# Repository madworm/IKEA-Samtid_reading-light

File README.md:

IKEA-Samtid_reading-light (WIP)
===============================

LAYOUT FILES: Circuit board to go between the movable beams of the Samtid lamp.

---

Before having PC-boards made, please make sure you know about your manufacturer's peculiarities!
Especially drill-sizes and their tolerances may vary too much and give you trouble.

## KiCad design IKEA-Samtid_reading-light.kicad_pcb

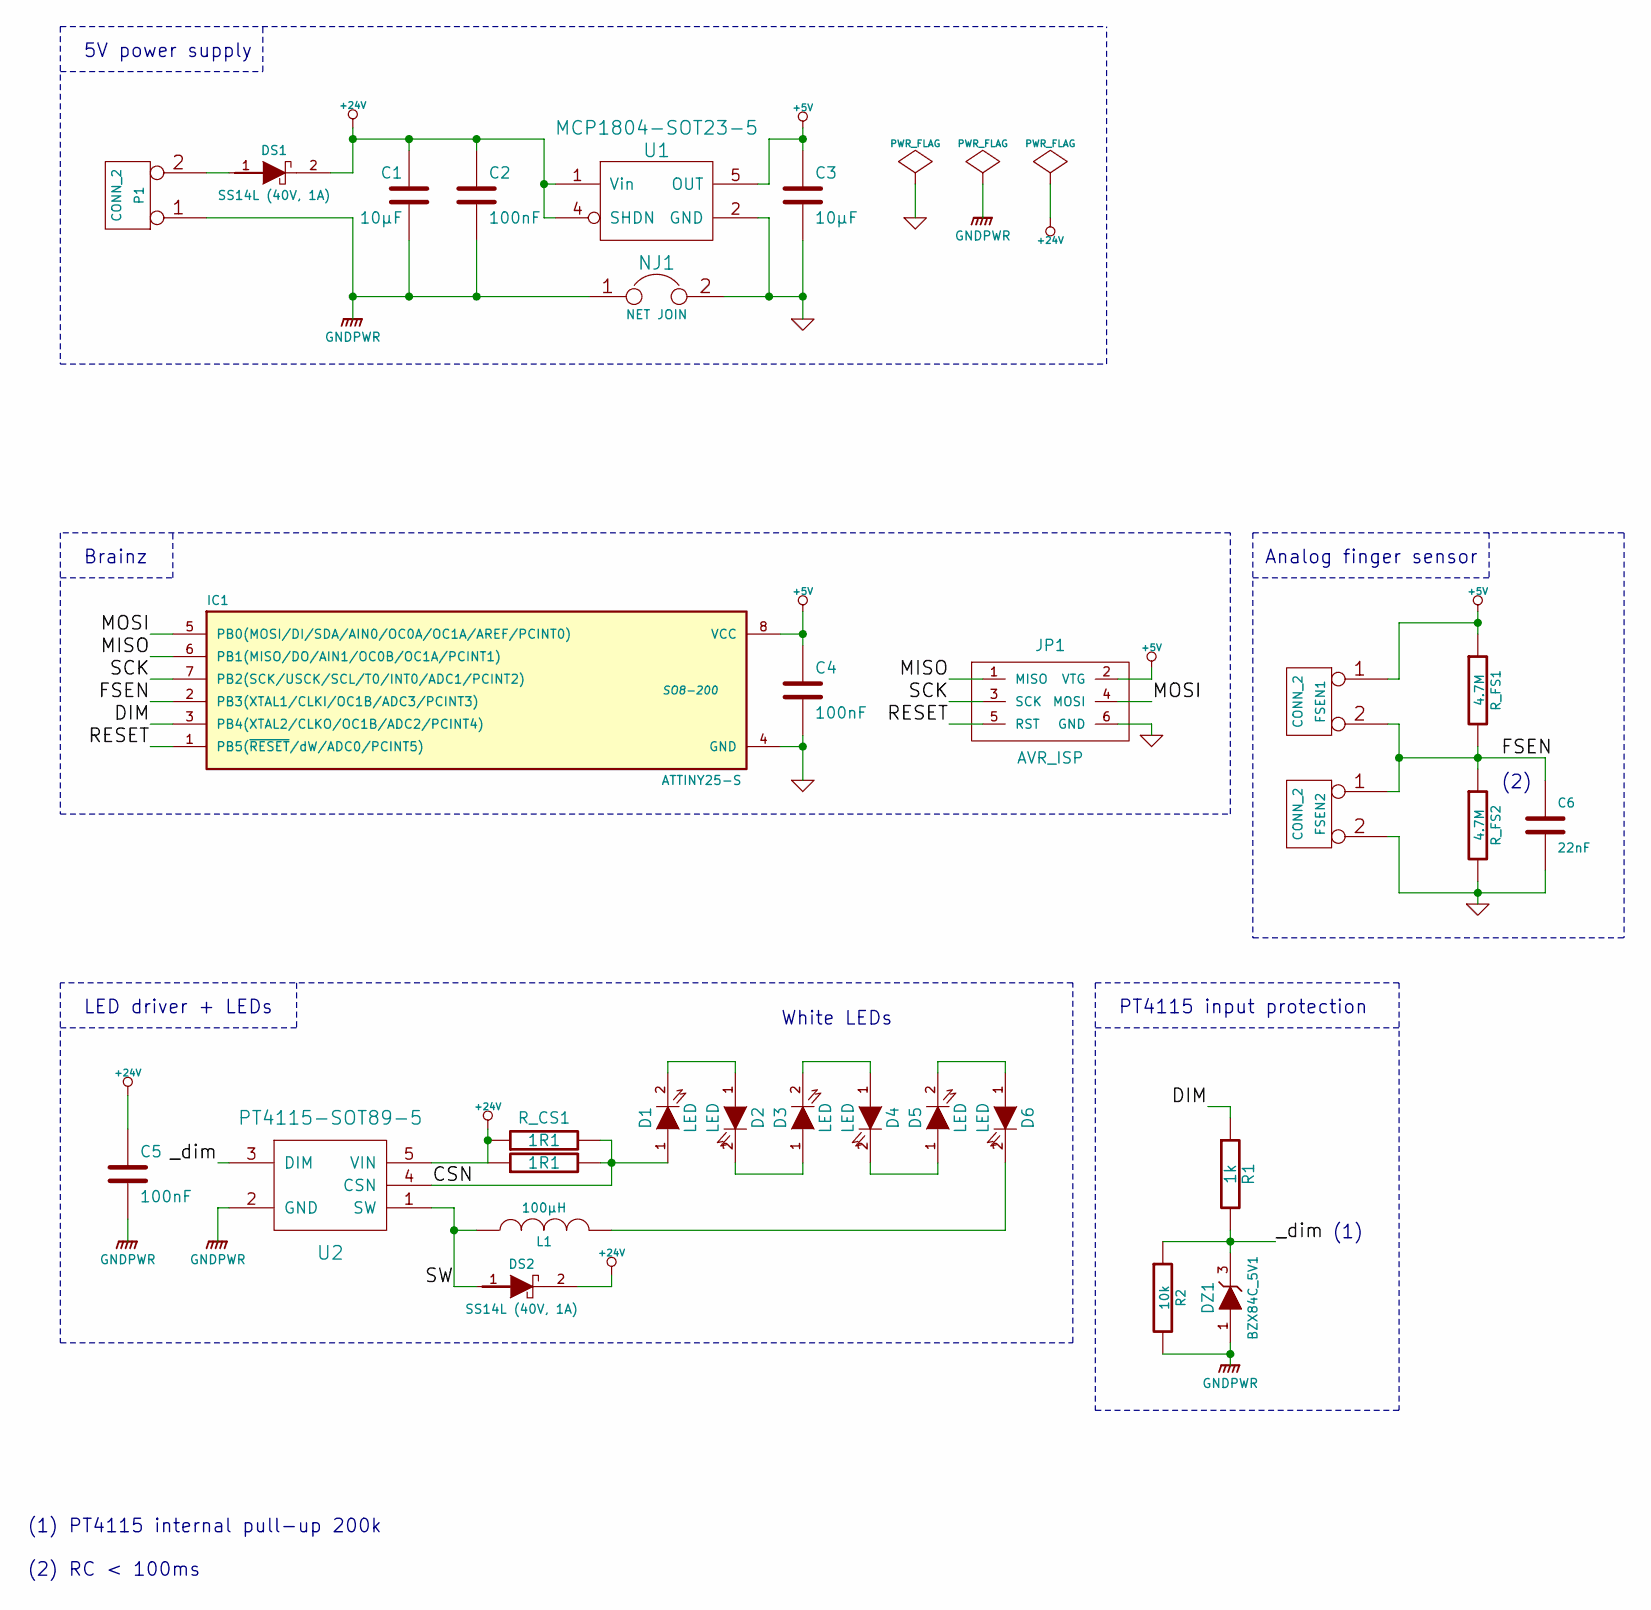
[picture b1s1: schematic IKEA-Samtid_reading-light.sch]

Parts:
C1, C3: 10µF
C2, C4, C5: 100nF
C6: 22nF
D1, D2, D3, D4, D5, D6: LED
DS1, DS2: SS14L (40V, 1A)
DZ1: BZX84C_5V1
FSEN1, FSEN2: CONN_2
IC1: ATTINY25-S; SO8-200
JP1: AVR_ISP
L1: 100µH
NJ1: NET JOIN
P1: CONN_2
R1: 1k
R2: 10k
R_CS1, R_CS2: 1R1
R_FS1, R_FS2: 4.7M
U1: MCP1804-SOT23-5
U2: PT4115-SOT89-5

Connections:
+5V: C3.1, C4.1, FSEN1.1, IC1.8 (VCC), JP1.2 (VTG), R_FS1.1, U1.5 (OUT)
+24V: C1.1, C2.1, C5.1, DS1.2 (C), DS2.2 (C), R_CS1.1, R_CS2.1, U1.1 (Vin), U1.4 (SHDN), U2.5 (VIN)
/CSN: D1.1 (A), R_CS1.2, R_CS2.2, U2.4 (CSN)
/DIM: IC1.3 (PB4(XTAL2/CLKO/OC1B/ADC2/PCINT4)), R1.1
/FSEN: C6.1, FSEN1.2 (PM), FSEN2.1, IC1.2 (PB3(XTAL1/CLKI/OC1B/ADC3/PCINT3)), R_FS1.2, R_FS2.1
/MISO: IC1.6 (PB1(MISO/DO/AIN1/OC0B/OC1A/PCINT1)), JP1.1 (MISO)
/MOSI: IC1.5 (PB0(MOSI/DI/SDA/AIN0/OC0A/OC1A/AREF/PCI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), JP1.4 (MOSI)
/RESET: IC1.1 (PB5(~RESET~/dW/ADC0/PCINT5)), JP1.5 (RST)
/SCK: IC1.7 (PB2(SCK/USCK/SCL/T0/INT0/ADC1/PCINT2)), JP1.3 (SCK)
/SW: DS2.1 (A), L1.1, U2.1 (SW)
/_dim: DZ1.3, R1.2, R2.1, U2.3 (DIM)
GND: C3.2, C4.2, C6.2, FSEN2.2 (PM), IC1.4 (GND), JP1.6 (GND), NJ1.2, R_FS2.2, U1.2 (GND)
GNDPWR: C1.2, C2.2, C5.2, DZ1.1, NJ1.1, P1.1, R2.2, U2.2 (GND)
unnamed: D1.2 (K), D2.1 (A)
unnamed: D2.2 (K), D3.1 (A)
unnamed: D3.2 (K), D4.1 (A)
unnamed: D4.2 (K), D5.1 (A)
unnamed: D5.2 (K), D6.1 (A)
unnamed: D6.2 (K), L1.2
unnamed: DS1.1 (A), P1.2 (PM)

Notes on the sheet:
White LEDs
Analog finger sensor
5V power supply
PT4115 input protection
Brainz
LED driver + LEDs
(1) PT4115 internal pull-up 200k (2) RC < 100ms
(1)
(2)

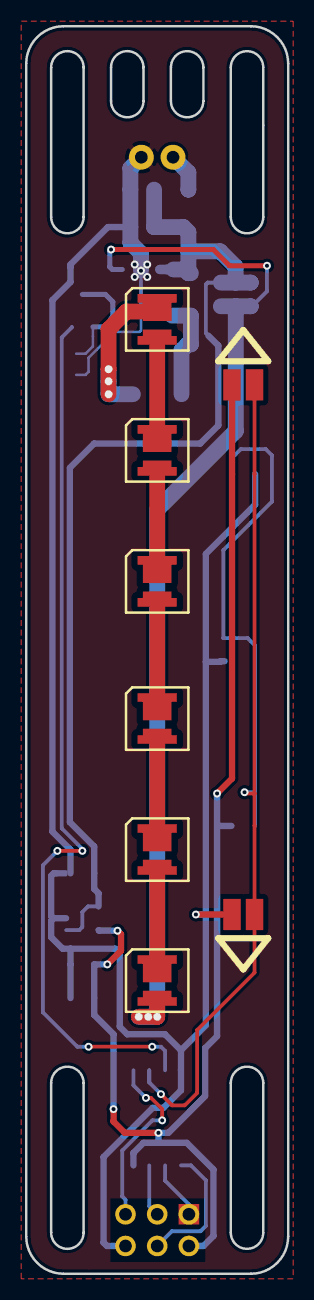
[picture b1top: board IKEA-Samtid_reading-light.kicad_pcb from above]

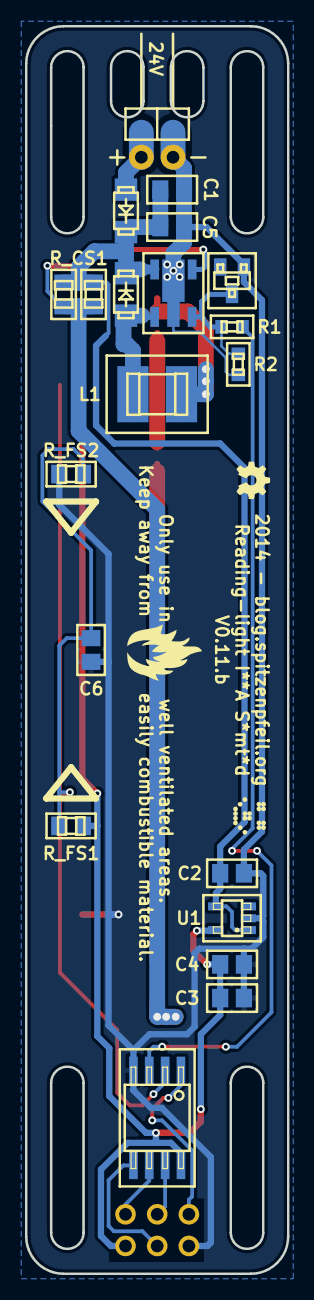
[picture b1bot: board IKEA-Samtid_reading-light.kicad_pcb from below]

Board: 2 copper layers, 21.0 x 100.0 mm, 33 parts (24 on the bottom side), 20 nets.

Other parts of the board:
LOGO1: LED_smile_silkscreen_3mm
LOGO2: OSHW-logo_silkscreen_3mm
LOGO3: fire_silkscreen-back_6mm

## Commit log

2014-05-27 Chose ATtiny25 for high-speed PWM (PLL).
2014-05-27 Shoving parts around.
2014-05-28 1st fully routed board (quite chaotic).
2014-05-28 Moved layer-alignment mark to Eco1.User layer.
2014-05-28 Routing + copper pour.
2014-05-28 Back to 100mil AVR_ISP header + layout tweaks.
2014-05-28 7mm --> 12mm slots (for 10mm tape) + shoved stuff around a bit.
2014-05-28 Tweaks.
2014-05-28 Added slots for zip-ties.
2014-05-28 Shoved parts around a bit. Visually more pleasing now.
2014-05-28 R_FSx 1M --> 10M.
2014-05-29 Striving for more horizontal symmetry.
2014-05-29 Added a buffer-cap for the ADC input + minor layout tweaks.
2014-05-30 Moved sensor pads away from LEDs + improved power input footprint.
2014-05-30 ISP footprint tweaks. Mark pin #1 by square pad just on top layer.
2014-06-08 Added front/back images.
2014-06-20 Fixed wrong 5V regulator footprint. SOT23-5 was needed, used SOT23-6 :-(
    Quick fix for prev. boards: solder-bridge from pin #6 to pin #5 (SOT23-6 footprint).
2014-06-21 Added a safety warning to silkscreen. This board gets quite hot.
2014-06-21 Updated 'README.md' + added 'Docs' folder.
2014-06-21 Updated PNGs.
2014-06-21 Tweaks.
    1) C6: 100nF --> 22nF (faster response to finger touch). RC < 100ms.
    2) Added 10k pull-down for _dim on PT4115 to prevent / reduce LED flash on power-up.
2014-06-22 Added comment to schematic (ATtiny13 vs. ATtiny25/45/85).
2014-06-25 Silkscreen tweaks.
2014-06-30 Some visibility settings were odd. Fixed that.
2014-07-07 Swapped R_FS1 & R_FS2 on PCB for same up/down operation front/back.
